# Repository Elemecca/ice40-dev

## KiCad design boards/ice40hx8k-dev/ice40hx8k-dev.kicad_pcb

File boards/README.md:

## Copying

Copyright 2022 Sam Hanes

The documentation in this directory describes Open Hardware and is
licensed under the CERN-OHL-S version 2 or any later version.

You may redistribute and modify this source and make products using it
under the terms of the [CERN-OHL-S v2](https://ohwr.org/cern_ohl_s_v2.txt).

This source is distributed WITHOUT ANY EXPRESS OR IMPLIED WARRANTY,
INCLUDING OF MERCHANTABILITY, SATISFACTORY QUALITY AND FITNESS FOR
A PARTICULAR PURPOSE. Please see the CERN-OHL-S v2 for applicable
conditions.

Source location: https://github.com/Elemecca/ice40-dev

As per CERN-OHL-S v2 section 4, should You produce hardware based
on this source, You must where practicable maintain the Source Location
visible on the external case of the products you make using this source.

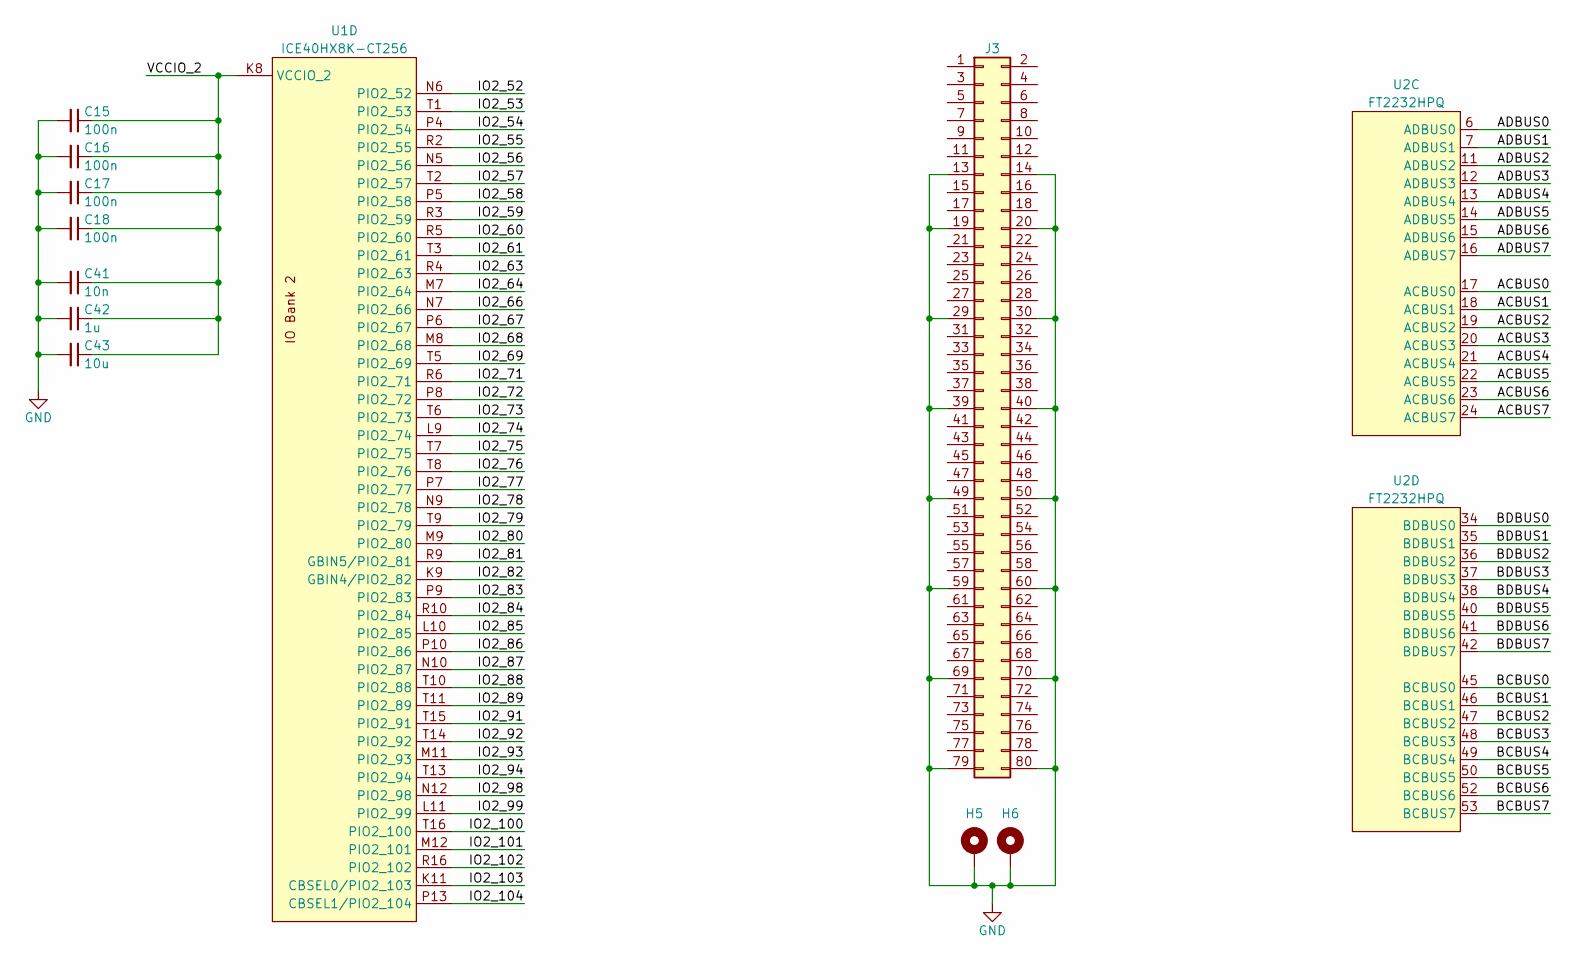
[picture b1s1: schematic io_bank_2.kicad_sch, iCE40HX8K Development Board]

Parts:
C15, C16, C17, C18: 100n; C_SMD_0402_Pad0.5mm
C41: 10n; C_SMD_0402_Pad0.5mm
C42: 1u; C_SMD_0402_Pad0.5mm
C43: 10u; C_SMD_0402_Pad0.5mm
H5, H6: 9774020633; MountingHole_2.2mm_M2_Pad6mm
J3: DF40HC(4.0)-80DS; Hirose_DF40C-80DS
U1: ICE40HX8K-CT256; Lattice_caBGA-256_14x14mm_Layout16x16_P0.8mm_Ball0.4mm_Pad0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
U2: FT2232HPQ; QFN-68-1EP_8x8mm_P0.4mm_EP5.2x5.2mm

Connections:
/IO_Bank_2/ACBUS0: U2.17 (ACBUS0)
/IO_Bank_2/ACBUS1: U2.18 (ACBUS1)
/IO_Bank_2/ACBUS2: U2.19 (ACBUS2)
/IO_Bank_2/ACBUS3: U2.20 (ACBUS3)
/IO_Bank_2/ACBUS4: U2.21 (ACBUS4)
/IO_Bank_2/ACBUS5: U2.22 (ACBUS5)
/IO_Bank_2/ACBUS6: U2.23 (ACBUS6)
/IO_Bank_2/ACBUS7: U2.24 (ACBUS7)
/IO_Bank_2/ADBUS0: U2.6 (ADBUS0)
/IO_Bank_2/ADBUS1: U2.7 (ADBUS1)
/IO_Bank_2/ADBUS2: U2.11 (ADBUS2)
/IO_Bank_2/ADBUS3: U2.12 (ADBUS3)
/IO_Bank_2/ADBUS4: U2.13 (ADBUS4)
/IO_Bank_2/ADBUS5: U2.14 (ADBUS5)
/IO_Bank_2/ADBUS6: U2.15 (ADBUS6)
/IO_Bank_2/ADBUS7: U2.16 (ADBUS7)
/IO_Bank_2/BCBUS0: U2.45 (BCBUS0)
/IO_Bank_2/BCBUS1: U2.46 (BCBUS1)
/IO_Bank_2/BCBUS2: U2.47 (BCBUS2)
/IO_Bank_2/BCBUS3: U2.48 (BCBUS3)
/IO_Bank_2/BCBUS4: U2.49 (BCBUS4)
/IO_Bank_2/BCBUS5: U2.50 (BCBUS5)
/IO_Bank_2/BCBUS6: U2.52 (BCBUS6)
/IO_Bank_2/BCBUS7: U2.53 (BCBUS7)
/IO_Bank_2/BDBUS0: U2.34 (BDBUS0)
/IO_Bank_2/BDBUS1: U2.35 (BDBUS1)
/IO_Bank_2/BDBUS2: U2.36 (BDBUS2)
/IO_Bank_2/BDBUS3: U2.37 (BDBUS3)
/IO_Bank_2/BDBUS4: U2.38 (BDBUS4)
/IO_Bank_2/BDBUS5: U2.40 (BDBUS5)
/IO_Bank_2/BDBUS6: U2.41 (BDBUS6)
/IO_Bank_2/BDBUS7: U2.42 (BDBUS7)
/IO_Bank_2/IO2_52: U1.N6 (PIO2_52)
/IO_Bank_2/IO2_53: U1.T1 (PIO2_53)
/IO_Bank_2/IO2_54: U1.P4 (PIO2_54)
/IO_Bank_2/IO2_55: U1.R2 (PIO2_55)
/IO_Bank_2/IO2_56: U1.N5 (PIO2_56)
/IO_Bank_2/IO2_57: U1.T2 (PIO2_57)
/IO_Bank_2/IO2_58: U1.P5 (PIO2_58)
/IO_Bank_2/IO2_59: U1.R3 (PIO2_59)
/IO_Bank_2/IO2_60: U1.R5 (PIO2_60)
/IO_Bank_2/IO2_61: U1.T3 (PIO2_61)
/IO_Bank_2/IO2_63: U1.R4 (PIO2_63)
/IO_Bank_2/IO2_64: U1.M7 (PIO2_64)
/IO_Bank_2/IO2_66: U1.N7 (PIO2_66)
/IO_Bank_2/IO2_67: U1.P6 (PIO2_67)
/IO_Bank_2/IO2_68: U1.M8 (PIO2_68)
/IO_Bank_2/IO2_69: U1.T5 (PIO2_69)
/IO_Bank_2/IO2_71: U1.R6 (PIO2_71)
/IO_Bank_2/IO2_72: U1.P8 (PIO2_72)
/IO_Bank_2/IO2_73: U1.T6 (PIO2_73)
/IO_Bank_2/IO2_74: U1.L9 (PIO2_74)
/IO_Bank_2/IO2_75: U1.T7 (PIO2_75)
/IO_Bank_2/IO2_76: U1.T8 (PIO2_76)
/IO_Bank_2/IO2_77: U1.P7 (PIO2_77)
/IO_Bank_2/IO2_78: U1.N9 (PIO2_78)
/IO_Bank_2/IO2_79: U1.T9 (PIO2_79)
/IO_Bank_2/IO2_80: U1.M9 (PIO2_80)
/IO_Bank_2/IO2_81: U1.R9 (GBIN5/PIO2_81)
/IO_Bank_2/IO2_82: U1.K9 (GBIN4/PIO2_82)
/IO_Bank_2/IO2_83: U1.P9 (PIO2_83)
/IO_Bank_2/IO2_84: U1.R10 (PIO2_84)
/IO_Bank_2/IO2_85: U1.L10 (PIO2_85)
/IO_Bank_2/IO2_86: U1.P10 (PIO2_86)
/IO_Bank_2/IO2_87: U1.N10 (PIO2_87)
/IO_Bank_2/IO2_88: U1.T10 (PIO2_88)
/IO_Bank_2/IO2_89: U1.T11 (PIO2_89)
/IO_Bank_2/IO2_91: U1.T15 (PIO2_91)
/IO_Bank_2/IO2_92: U1.T14 (PIO2_92)
/IO_Bank_2/IO2_93: U1.M11 (PIO2_93)
/IO_Bank_2/IO2_94: U1.T13 (PIO2_94)
/IO_Bank_2/IO2_98: U1.N12 (PIO2_98)
/IO_Bank_2/IO2_99: U1.L11 (PIO2_99)
/IO_Bank_2/IO2_100: U1.T16 (PIO2_100)
/IO_Bank_2/IO2_101: U1.M12 (PIO2_101)
/IO_Bank_2/IO2_102: U1.R16 (PIO2_102)
/IO_Bank_2/IO2_103: U1.K11 (CBSEL0/PIO2_103)
/IO_Bank_2/IO2_104: U1.P13 (CBSEL1/PIO2_104)
/IO_Bank_2/VCCIO_2: C15.1, C16.1, C17.1, C18.1, C41.1, C42.1, C43.1, U1.K8 (VCCIO_2), U1.P3 (VCCIO_2), U1.R8 (VCCIO_2), U1.R13 (VCCIO_2)
GND: C15.2, C16.2, C17.2, C18.2, C41.2, C42.2, C43.2, H5.1, H6.1, J3.13, J3.14, J3.19, J3.20, J3.29, J3.30, J3.39, J3.40, J3.49, J3.50, J3.59, J3.60, J3.69, J3.70, J3.79, J3.80; also elsewhere on the board

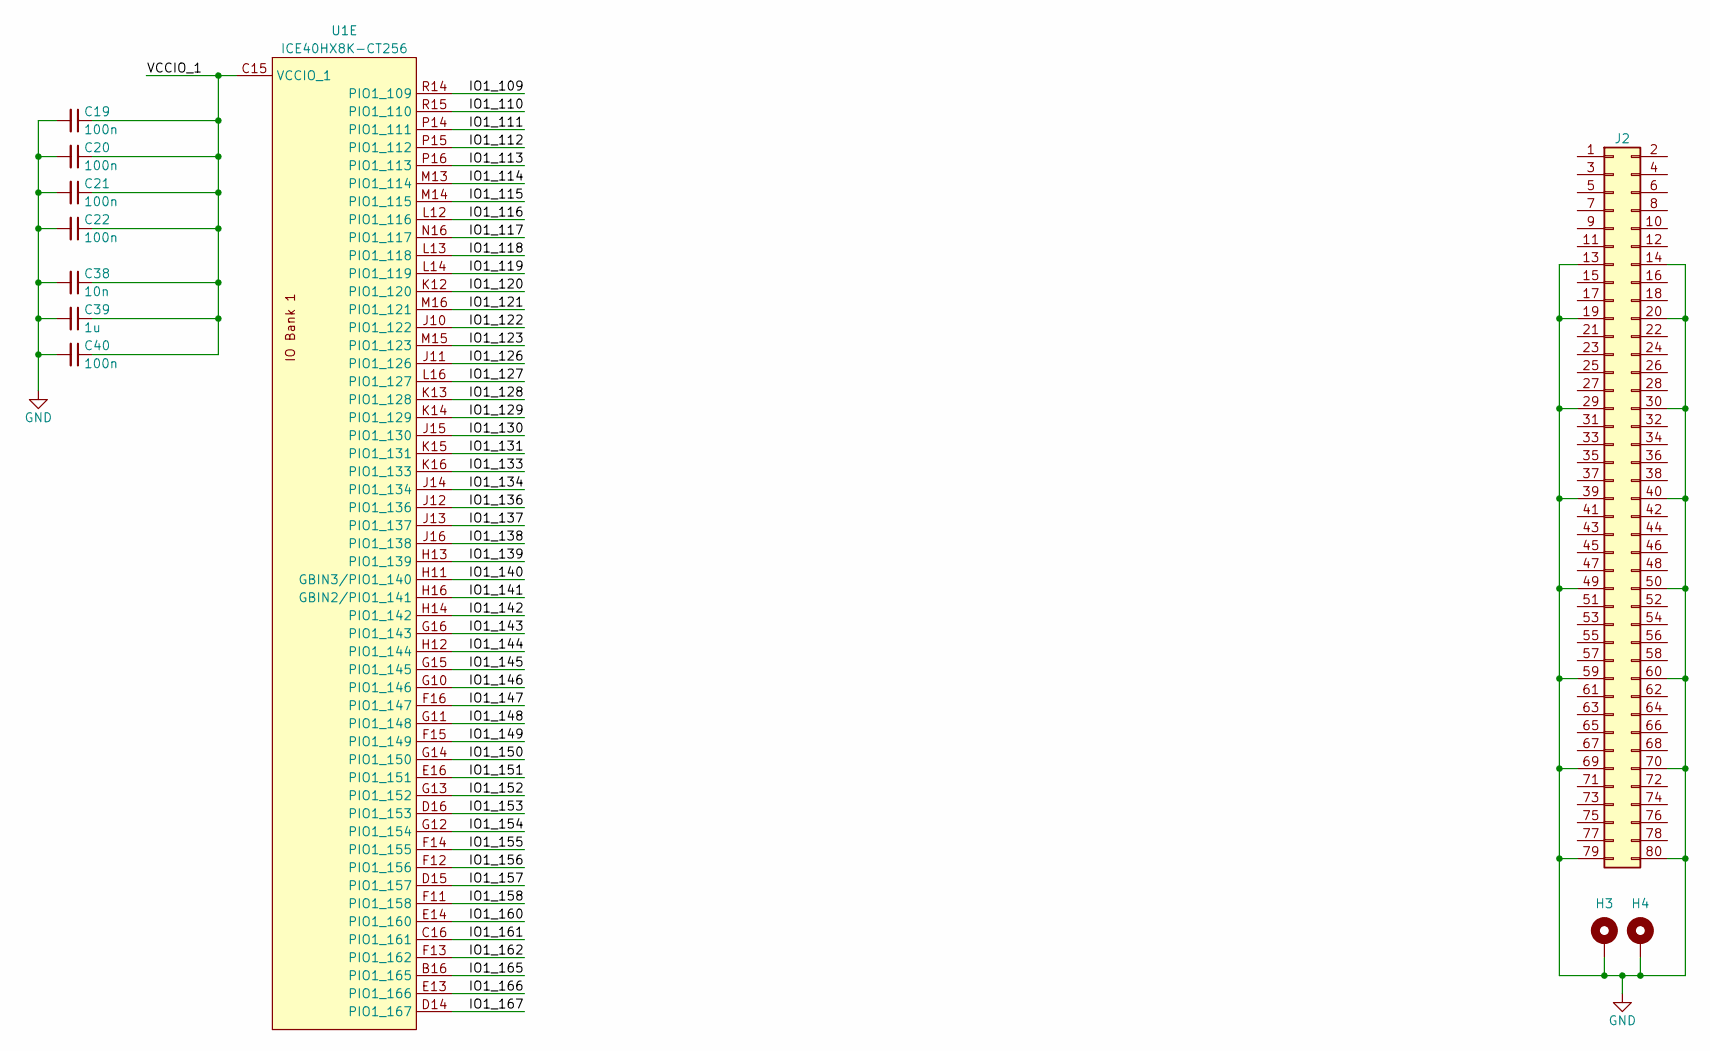
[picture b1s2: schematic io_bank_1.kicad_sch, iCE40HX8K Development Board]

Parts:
C19, C20, C21, C22, C40: 100n; C_SMD_0402_Pad0.5mm
C38: 10n; C_SMD_0402_Pad0.5mm
C39: 1u; C_SMD_0402_Pad0.5mm
H3, H4: 9774020633; MountingHole_2.2mm_M2_Pad6mm
J2: DF40HC(4.0)-80DS; Hirose_DF40C-80DS
U1: ICE40HX8K-CT256; Lattice_caBGA-256_14x14mm_Layout16x16_P0.8mm_Ball0.4mm_Pad0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

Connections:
/IO_Bank_1/IO1_109: U1.R14 (PIO1_109)
/IO_Bank_1/IO1_110: U1.R15 (PIO1_110)
/IO_Bank_1/IO1_111: U1.P14 (PIO1_111)
/IO_Bank_1/IO1_112: U1.P15 (PIO1_112)
/IO_Bank_1/IO1_113: U1.P16 (PIO1_113)
/IO_Bank_1/IO1_114: U1.M13 (PIO1_114)
/IO_Bank_1/IO1_115: U1.M14 (PIO1_115)
/IO_Bank_1/IO1_116: U1.L12 (PIO1_116)
/IO_Bank_1/IO1_117: U1.N16 (PIO1_117)
/IO_Bank_1/IO1_118: U1.L13 (PIO1_118)
/IO_Bank_1/IO1_119: U1.L14 (PIO1_119)
/IO_Bank_1/IO1_120: U1.K12 (PIO1_120)
/IO_Bank_1/IO1_121: U1.M16 (PIO1_121)
/IO_Bank_1/IO1_122: U1.J10 (PIO1_122)
/IO_Bank_1/IO1_123: U1.M15 (PIO1_123)
/IO_Bank_1/IO1_126: U1.J11 (PIO1_126)
/IO_Bank_1/IO1_127: U1.L16 (PIO1_127)
/IO_Bank_1/IO1_128: U1.K13 (PIO1_128)
/IO_Bank_1/IO1_129: U1.K14 (PIO1_129)
/IO_Bank_1/IO1_130: U1.J15 (PIO1_130)
/IO_Bank_1/IO1_131: U1.K15 (PIO1_131)
/IO_Bank_1/IO1_133: U1.K16 (PIO1_133)
/IO_Bank_1/IO1_134: U1.J14 (PIO1_134)
/IO_Bank_1/IO1_136: U1.J12 (PIO1_136)
/IO_Bank_1/IO1_137: U1.J13 (PIO1_137)
/IO_Bank_1/IO1_138: U1.J16 (PIO1_138)
/IO_Bank_1/IO1_139: U1.H13 (PIO1_139)
/IO_Bank_1/IO1_140: U1.H11 (GBIN3/PIO1_140)
/IO_Bank_1/IO1_141: U1.H16 (GBIN2/PIO1_141)
/IO_Bank_1/IO1_142: U1.H14 (PIO1_142)
/IO_Bank_1/IO1_143: U1.G16 (PIO1_143)
/IO_Bank_1/IO1_144: U1.H12 (PIO1_144)
/IO_Bank_1/IO1_145: U1.G15 (PIO1_145)
/IO_Bank_1/IO1_146: U1.G10 (PIO1_146)
/IO_Bank_1/IO1_147: U1.F16 (PIO1_147)
/IO_Bank_1/IO1_148: U1.G11 (PIO1_148)
/IO_Bank_1/IO1_149: U1.F15 (PIO1_149)
/IO_Bank_1/IO1_150: U1.G14 (PIO1_150)
/IO_Bank_1/IO1_151: U1.E16 (PIO1_151)
/IO_Bank_1/IO1_152: U1.G13 (PIO1_152)
/IO_Bank_1/IO1_153: U1.D16 (PIO1_153)
/IO_Bank_1/IO1_154: U1.G12 (PIO1_154)
/IO_Bank_1/IO1_155: U1.F14 (PIO1_155)
/IO_Bank_1/IO1_156: U1.F12 (PIO1_156)
/IO_Bank_1/IO1_157: U1.D15 (PIO1_157)
/IO_Bank_1/IO1_158: U1.F11 (PIO1_158)
/IO_Bank_1/IO1_160: U1.E14 (PIO1_160)
/IO_Bank_1/IO1_161: U1.C16 (PIO1_161)
/IO_Bank_1/IO1_162: U1.F13 (PIO1_162)
/IO_Bank_1/IO1_165: U1.B16 (PIO1_165)
/IO_Bank_1/IO1_166: U1.E13 (PIO1_166)
/IO_Bank_1/IO1_167: U1.D14 (PIO1_167)
/IO_Bank_1/VCCIO_1: C19.1, C20.1, C21.1, C22.1, C38.1, C39.1, C40.1, U1.C15 (VCCIO_1), U1.H10 (VCCIO_1), U1.H15 (VCCIO_1), U1.N15 (VCCIO_1)
GND: C19.2, C20.2, C21.2, C22.2, C38.2, C39.2, C40.2, H3.1, H4.1, J2.13, J2.14, J2.19, J2.20, J2.29, J2.30, J2.39, J2.40, J2.49, J2.50, J2.59, J2.60, J2.69, J2.70, J2.79, J2.80; also elsewhere on the board

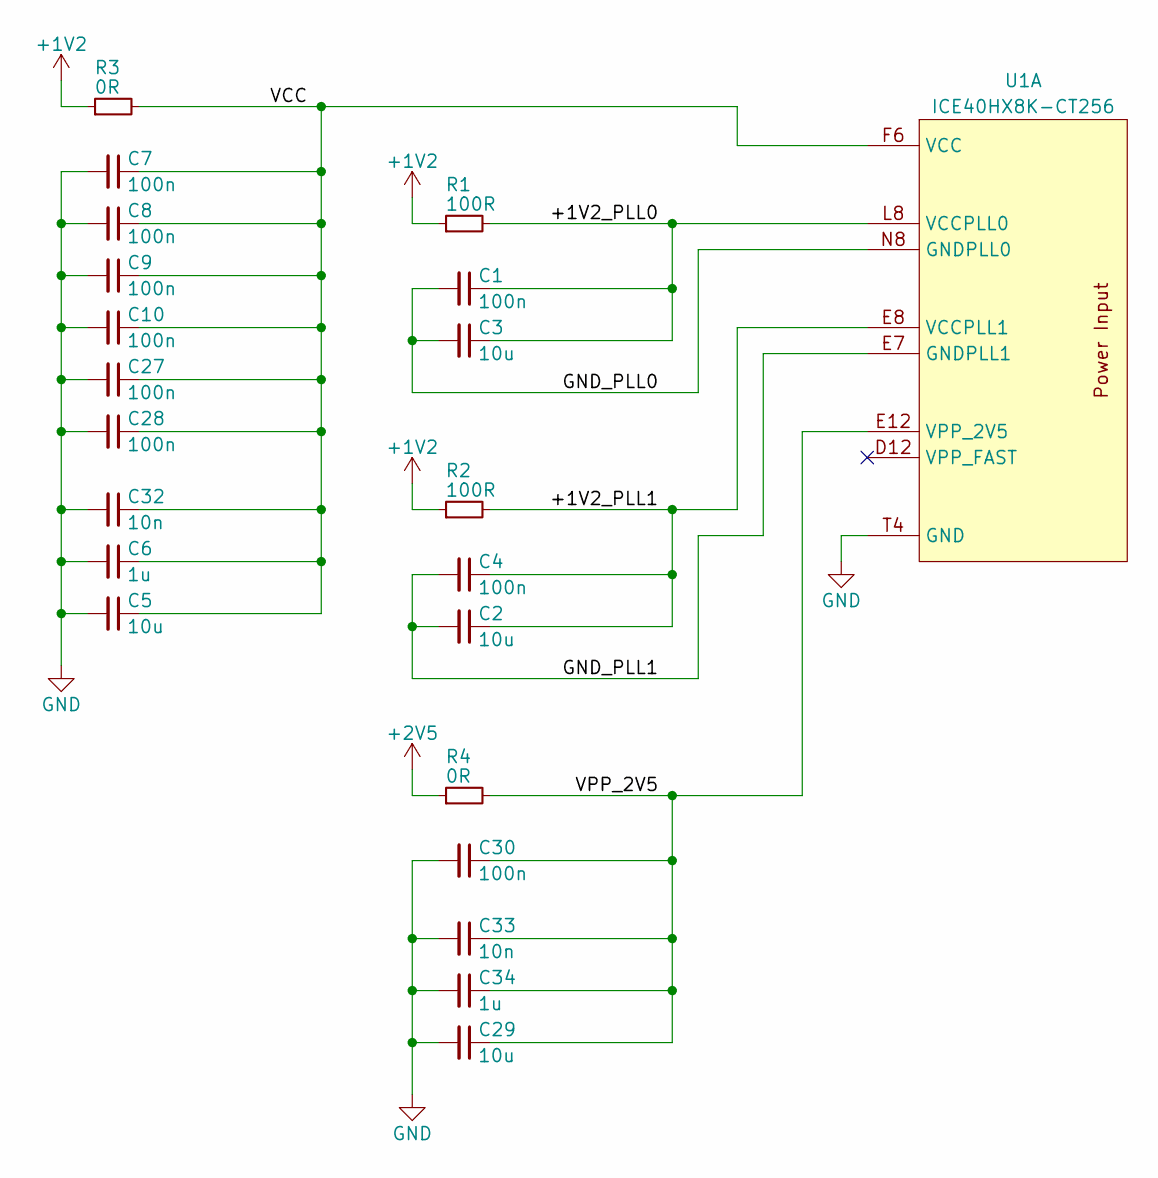
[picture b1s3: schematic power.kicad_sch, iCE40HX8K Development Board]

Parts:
C1, C4, C7, C8, C9, C10, C27, C28, C30: 100n; C_SMD_0402_Pad0.5mm
C2, C3, C5, C29: 10u; C_SMD_0402_Pad0.5mm
C6, C34: 1u; C_SMD_0402_Pad0.5mm
C32, C33: 10n; C_SMD_0402_Pad0.5mm
R1, R2: 100R; R_SMD_0402_Pad0.5mm
R3, R4: 0R; R_SMD_0402_Pad0.5mm
U1: ICE40HX8K-CT256; Lattice_caBGA-256_14x14mm_Layout16x16_P0.8mm_Ball0.4mm_Pad0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

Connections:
+1V2: R1.1, R2.1, R3.1
+2V5: R4.1
/Power/+1V2_PLL0: C1.1, C3.1, R1.2, U1.L8 (VCCPLL0)
/Power/+1V2_PLL1: C2.1, C4.1, R2.2, U1.E8 (VCCPLL1)
/Power/GND_PLL0: C1.2, C3.2, U1.N8 (GNDPLL0)
/Power/GND_PLL1: C2.2, C4.2, U1.E7 (GNDPLL1)
/Power/VCC: C5.1, C6.1, C7.1, C8.1, C9.1, C10.1, C27.1, C28.1, C32.1, R3.2, U1.A14 (VCC), U1.F6 (VCC), U1.F10 (VCC), U1.K6 (VCC), U1.K10 (VCC), U1.L2 (VCC)
/Power/VPP_2V5: C29.1, C30.1, C33.1, C34.1, R4.2, U1.E12 (VPP_2V5)
GND: C5.2, C6.2, C7.2, C8.2, C9.2, C10.2, C27.2, C28.2, C29.2, C30.2, C32.2, C33.2, C34.2, U1.A4 (GND), U1.A12 (GND), U1.E15 (GND), U1.G7 (GND), U1.G8 (GND), U1.G9 (GND), U1.H7 (GND), U1.H8 (GND), U1.H9 (GND), U1.J7 (GND), U1.J8 (GND), U1.J9 (GND), U1.K2 (GND), U1.K7 (GND), U1.L15 (GND), U1.R7 (GND), U1.T4 (GND), U1.T12 (GND); also elsewhere on the board

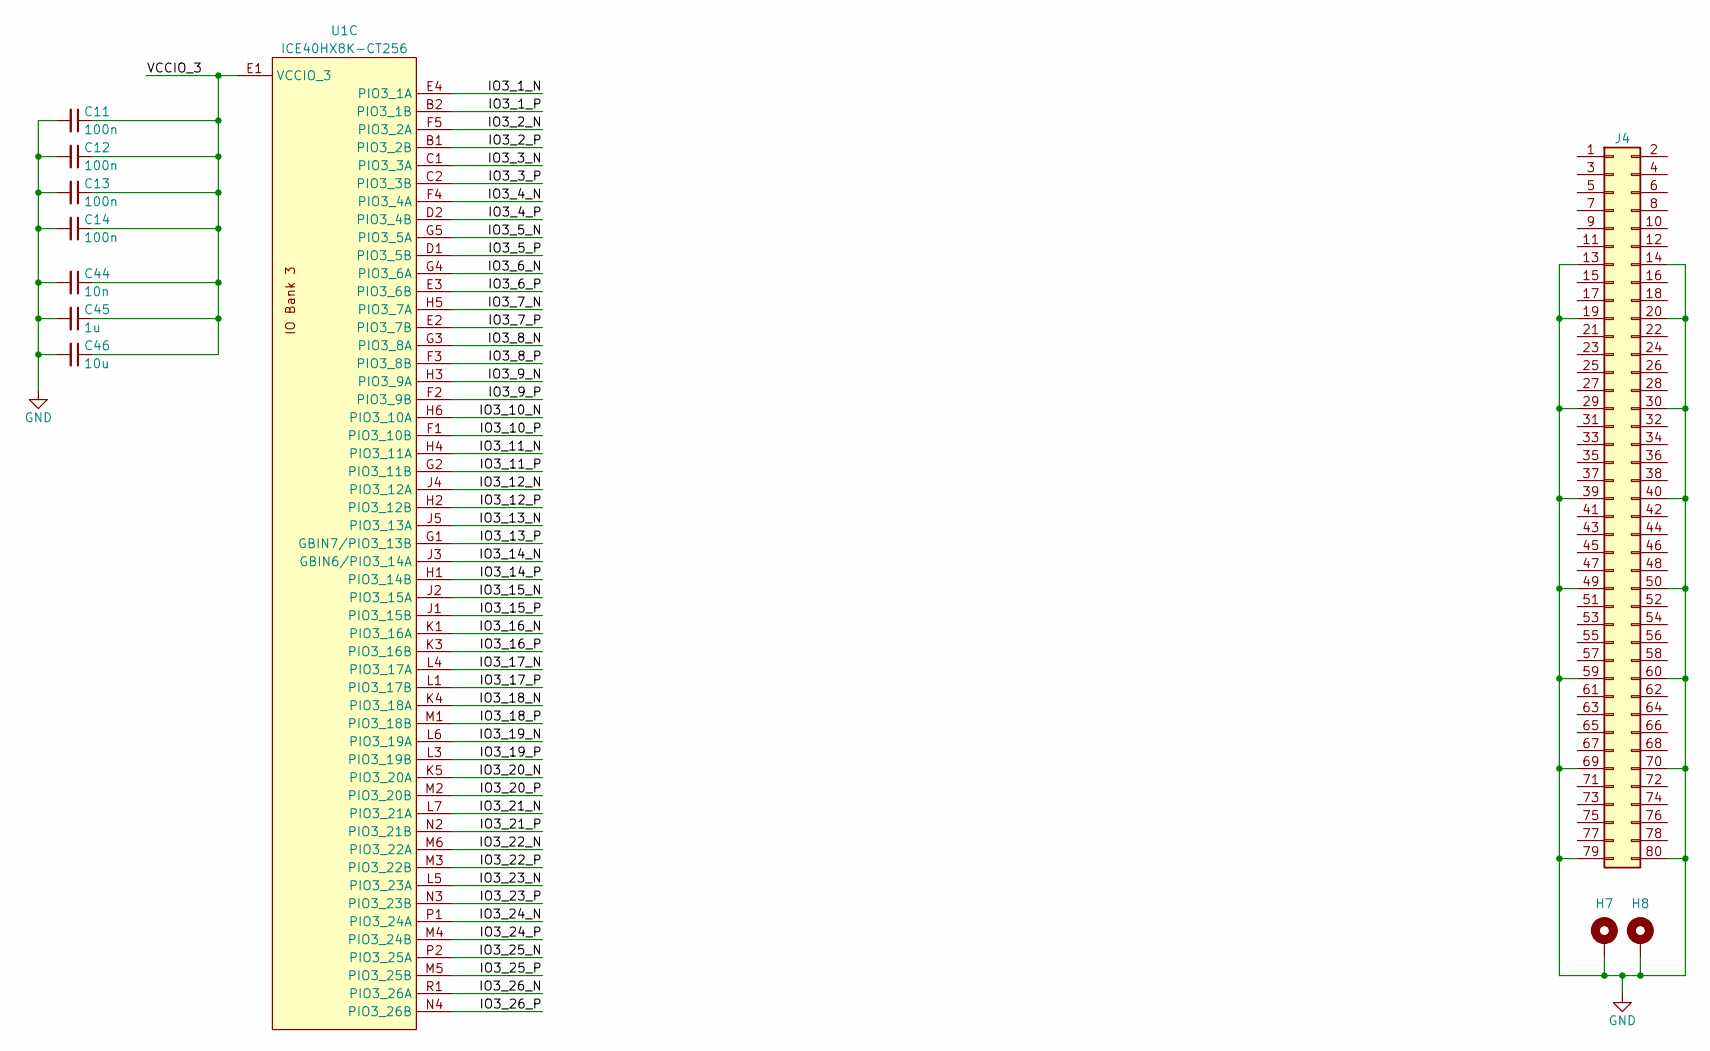
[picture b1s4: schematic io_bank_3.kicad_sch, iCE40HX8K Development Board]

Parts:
C11, C12, C13, C14: 100n; C_SMD_0402_Pad0.5mm
C44: 10n; C_SMD_0402_Pad0.5mm
C45: 1u; C_SMD_0402_Pad0.5mm
C46: 10u; C_SMD_0402_Pad0.5mm
H7, H8: 9774020633; MountingHole_2.2mm_M2_Pad6mm
J4: DF40HC(4.0)-80DS; Hirose_DF40C-80DS
U1: ICE40HX8K-CT256; Lattice_caBGA-256_14x14mm_Layout16x16_P0.8mm_Ball0.4mm_Pad0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

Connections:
/IO_Bank_3/IO3_1_N: U1.E4 (PIO3_1A)
/IO_Bank_3/IO3_1_P: U1.B2 (PIO3_1B)
/IO_Bank_3/IO3_2_N: U1.F5 (PIO3_2A)
/IO_Bank_3/IO3_2_P: U1.B1 (PIO3_2B)
/IO_Bank_3/IO3_3_N: U1.C1 (PIO3_3A)
/IO_Bank_3/IO3_3_P: U1.C2 (PIO3_3B)
/IO_Bank_3/IO3_4_N: U1.F4 (PIO3_4A)
/IO_Bank_3/IO3_4_P: U1.D2 (PIO3_4B)
/IO_Bank_3/IO3_5_N: U1.G5 (PIO3_5A)
/IO_Bank_3/IO3_5_P: U1.D1 (PIO3_5B)
/IO_Bank_3/IO3_6_N: U1.G4 (PIO3_6A)
/IO_Bank_3/IO3_6_P: U1.E3 (PIO3_6B)
/IO_Bank_3/IO3_7_N: U1.H5 (PIO3_7A)
/IO_Bank_3/IO3_7_P: U1.E2 (PIO3_7B)
/IO_Bank_3/IO3_8_N: U1.G3 (PIO3_8A)
/IO_Bank_3/IO3_8_P: U1.F3 (PIO3_8B)
/IO_Bank_3/IO3_9_N: U1.H3 (PIO3_9A)
/IO_Bank_3/IO3_9_P: U1.F2 (PIO3_9B)
/IO_Bank_3/IO3_10_N: U1.H6 (PIO3_10A)
/IO_Bank_3/IO3_10_P: U1.F1 (PIO3_10B)
/IO_Bank_3/IO3_11_N: U1.H4 (PIO3_11A)
/IO_Bank_3/IO3_11_P: U1.G2 (PIO3_11B)
/IO_Bank_3/IO3_12_N: U1.J4 (PIO3_12A)
/IO_Bank_3/IO3_12_P: U1.H2 (PIO3_12B)
/IO_Bank_3/IO3_13_N: U1.J5 (PIO3_13A)
/IO_Bank_3/IO3_13_P: U1.G1 (GBIN7/PIO3_13B)
/IO_Bank_3/IO3_14_N: U1.J3 (GBIN6/PIO3_14A)
/IO_Bank_3/IO3_14_P: U1.H1 (PIO3_14B)
/IO_Bank_3/IO3_15_N: U1.J2 (PIO3_15A)
/IO_Bank_3/IO3_15_P: U1.J1 (PIO3_15B)
/IO_Bank_3/IO3_16_N: U1.K1 (PIO3_16A)
/IO_Bank_3/IO3_16_P: U1.K3 (PIO3_16B)
/IO_Bank_3/IO3_17_N: U1.L4 (PIO3_17A)
/IO_Bank_3/IO3_17_P: U1.L1 (PIO3_17B)
/IO_Bank_3/IO3_18_N: U1.K4 (PIO3_18A)
/IO_Bank_3/IO3_18_P: U1.M1 (PIO3_18B)
/IO_Bank_3/IO3_19_N: U1.L6 (PIO3_19A)
/IO_Bank_3/IO3_19_P: U1.L3 (PIO3_19B)
/IO_Bank_3/IO3_20_N: U1.K5 (PIO3_20A)
/IO_Bank_3/IO3_20_P: U1.M2 (PIO3_20B)
/IO_Bank_3/IO3_21_N: U1.L7 (PIO3_21A)
/IO_Bank_3/IO3_21_P: U1.N2 (PIO3_21B)
/IO_Bank_3/IO3_22_N: U1.M6 (PIO3_22A)
/IO_Bank_3/IO3_22_P: U1.M3 (PIO3_22B)
/IO_Bank_3/IO3_23_N: U1.L5 (PIO3_23A)
/IO_Bank_3/IO3_23_P: U1.N3 (PIO3_23B)
/IO_Bank_3/IO3_24_N: U1.P1 (PIO3_24A)
/IO_Bank_3/IO3_24_P: U1.M4 (PIO3_24B)
/IO_Bank_3/IO3_25_N: U1.P2 (PIO3_25A)
/IO_Bank_3/IO3_25_P: U1.M5 (PIO3_25B)
/IO_Bank_3/IO3_26_N: U1.R1 (PIO3_26A)
/IO_Bank_3/IO3_26_P: U1.N4 (PIO3_26B)
/IO_Bank_3/VCCIO_3: C11.1, C12.1, C13.1, C14.1, C44.1, C45.1, C46.1, U1.E1 (VCCIO_3), U1.G6 (VCCIO_3), U1.J6 (VCCIO_3), U1.N1 (VCCIO_3)
GND: C11.2, C12.2, C13.2, C14.2, C44.2, C45.2, C46.2, H7.1, H8.1, J4.13, J4.14, J4.19, J4.20, J4.29, J4.30, J4.39, J4.40, J4.49, J4.50, J4.59, J4.60, J4.69, J4.70, J4.79, J4.80; also elsewhere on the board

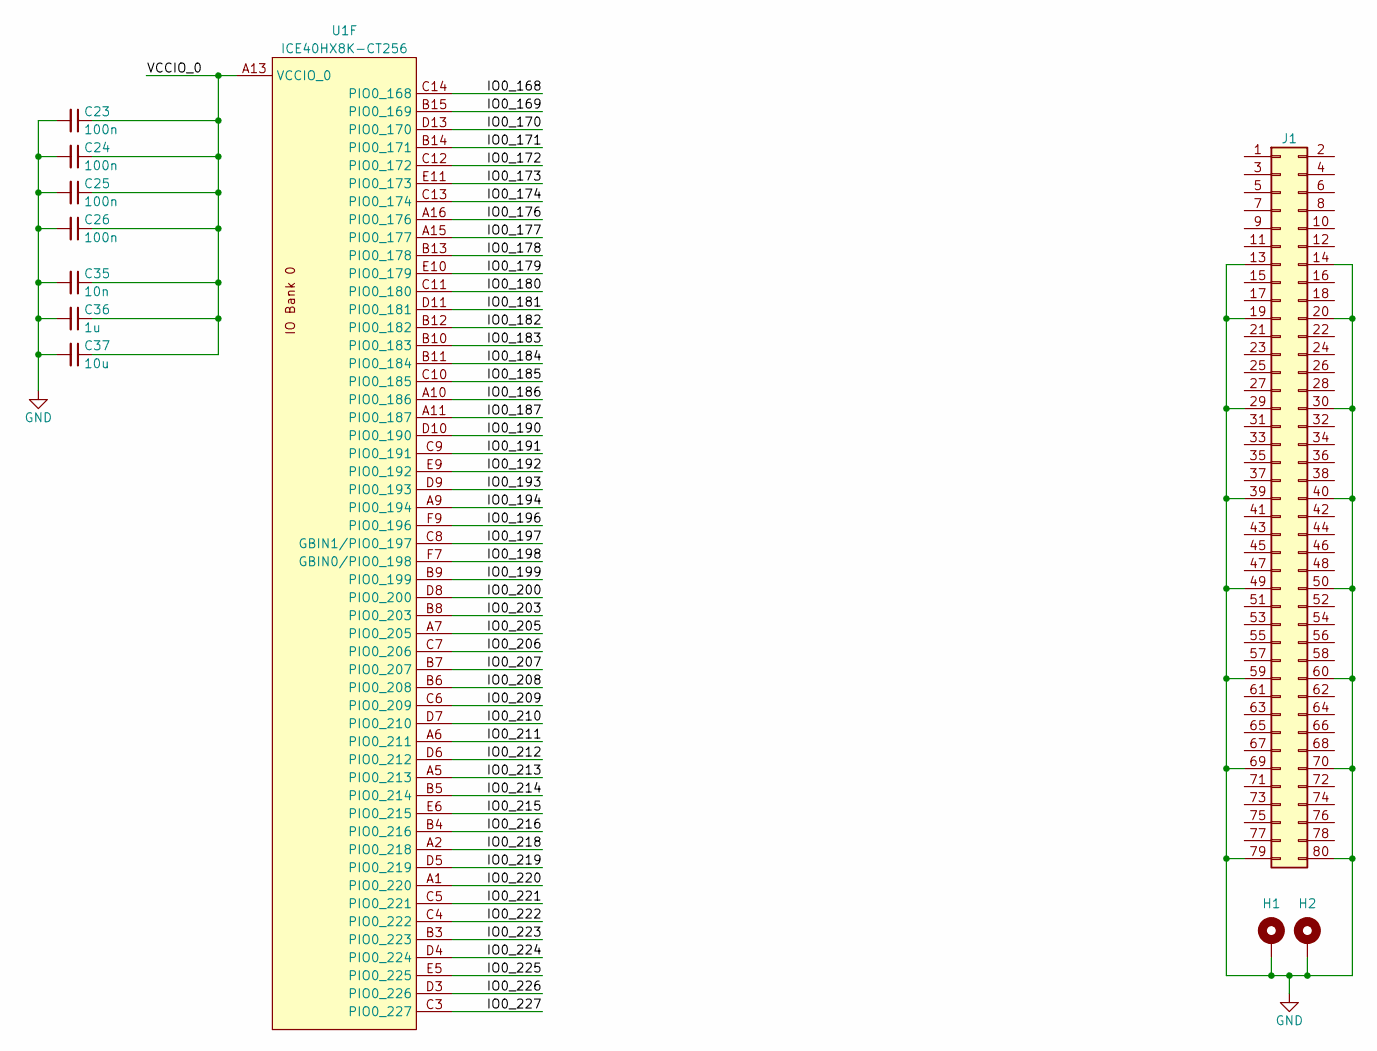
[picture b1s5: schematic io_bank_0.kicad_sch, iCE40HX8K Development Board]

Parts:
C23, C24, C25, C26: 100n; C_SMD_0402_Pad0.5mm
C35: 10n; C_SMD_0402_Pad0.5mm
C36: 1u; C_SMD_0402_Pad0.5mm
C37: 10u; C_SMD_0402_Pad0.5mm
H1, H2: 9774020633; MountingHole_2.2mm_M2_Pad6mm
J1: DF40HC(4.0)-80DS; Hirose_DF40C-80DS
U1: ICE40HX8K-CT256; Lattice_caBGA-256_14x14mm_Layout16x16_P0.8mm_Ball0.4mm_Pad0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

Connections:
/IO_Bank_0/IO0_168: U1.C14 (PIO0_168)
/IO_Bank_0/IO0_169: U1.B15 (PIO0_169)
/IO_Bank_0/IO0_170: U1.D13 (PIO0_170)
/IO_Bank_0/IO0_171: U1.B14 (PIO0_171)
/IO_Bank_0/IO0_172: U1.C12 (PIO0_172)
/IO_Bank_0/IO0_173: U1.E11 (PIO0_173)
/IO_Bank_0/IO0_174: U1.C13 (PIO0_174)
/IO_Bank_0/IO0_176: U1.A16 (PIO0_176)
/IO_Bank_0/IO0_177: U1.A15 (PIO0_177)
/IO_Bank_0/IO0_178: U1.B13 (PIO0_178)
/IO_Bank_0/IO0_179: U1.E10 (PIO0_179)
/IO_Bank_0/IO0_180: U1.C11 (PIO0_180)
/IO_Bank_0/IO0_181: U1.D11 (PIO0_181)
/IO_Bank_0/IO0_182: U1.B12 (PIO0_182)
/IO_Bank_0/IO0_183: U1.B10 (PIO0_183)
/IO_Bank_0/IO0_184: U1.B11 (PIO0_184)
/IO_Bank_0/IO0_185: U1.C10 (PIO0_185)
/IO_Bank_0/IO0_186: U1.A10 (PIO0_186)
/IO_Bank_0/IO0_187: U1.A11 (PIO0_187)
/IO_Bank_0/IO0_190: U1.D10 (PIO0_190)
/IO_Bank_0/IO0_191: U1.C9 (PIO0_191)
/IO_Bank_0/IO0_192: U1.E9 (PIO0_192)
/IO_Bank_0/IO0_193: U1.D9 (PIO0_193)
/IO_Bank_0/IO0_194: U1.A9 (PIO0_194)
/IO_Bank_0/IO0_196: U1.F9 (PIO0_196)
/IO_Bank_0/IO0_197: U1.C8 (GBIN1/PIO0_197)
/IO_Bank_0/IO0_198: U1.F7 (GBIN0/PIO0_198)
/IO_Bank_0/IO0_199: U1.B9 (PIO0_199)
/IO_Bank_0/IO0_200: U1.D8 (PIO0_200)
/IO_Bank_0/IO0_203: U1.B8 (PIO0_203)
/IO_Bank_0/IO0_205: U1.A7 (PIO0_205)
/IO_Bank_0/IO0_206: U1.C7 (PIO0_206)
/IO_Bank_0/IO0_207: U1.B7 (PIO0_207)
/IO_Bank_0/IO0_208: U1.B6 (PIO0_208)
/IO_Bank_0/IO0_209: U1.C6 (PIO0_209)
/IO_Bank_0/IO0_210: U1.D7 (PIO0_210)
/IO_Bank_0/IO0_211: U1.A6 (PIO0_211)
/IO_Bank_0/IO0_212: U1.D6 (PIO0_212)
/IO_Bank_0/IO0_213: U1.A5 (PIO0_213)
/IO_Bank_0/IO0_214: U1.B5 (PIO0_214)
/IO_Bank_0/IO0_215: U1.E6 (PIO0_215)
/IO_Bank_0/IO0_216: U1.B4 (PIO0_216)
/IO_Bank_0/IO0_218: U1.A2 (PIO0_218)
/IO_Bank_0/IO0_219: U1.D5 (PIO0_219)
/IO_Bank_0/IO0_220: U1.A1 (PIO0_220)
/IO_Bank_0/IO0_221: U1.C5 (PIO0_221)
/IO_Bank_0/IO0_222: U1.C4 (PIO0_222)
/IO_Bank_0/IO0_223: U1.B3 (PIO0_223)
/IO_Bank_0/IO0_224: U1.D4 (PIO0_224)
/IO_Bank_0/IO0_225: U1.E5 (PIO0_225)
/IO_Bank_0/IO0_226: U1.D3 (PIO0_226)
/IO_Bank_0/IO0_227: U1.C3 (PIO0_227)
/IO_Bank_0/VCCIO_0: C23.1, C24.1, C25.1, C26.1, C35.1, C36.1, C37.1, U1.A3 (VCCIO_0), U1.A8 (VCCIO_0), U1.A13 (VCCIO_0), U1.F8 (VCCIO_0)
GND: C23.2, C24.2, C25.2, C26.2, C35.2, C36.2, C37.2, H1.1, H2.1, J1.13, J1.14, J1.19, J1.20, J1.29, J1.30, J1.39, J1.40, J1.49, J1.50, J1.59, J1.60, J1.69, J1.70, J1.79, J1.80; also elsewhere on the board

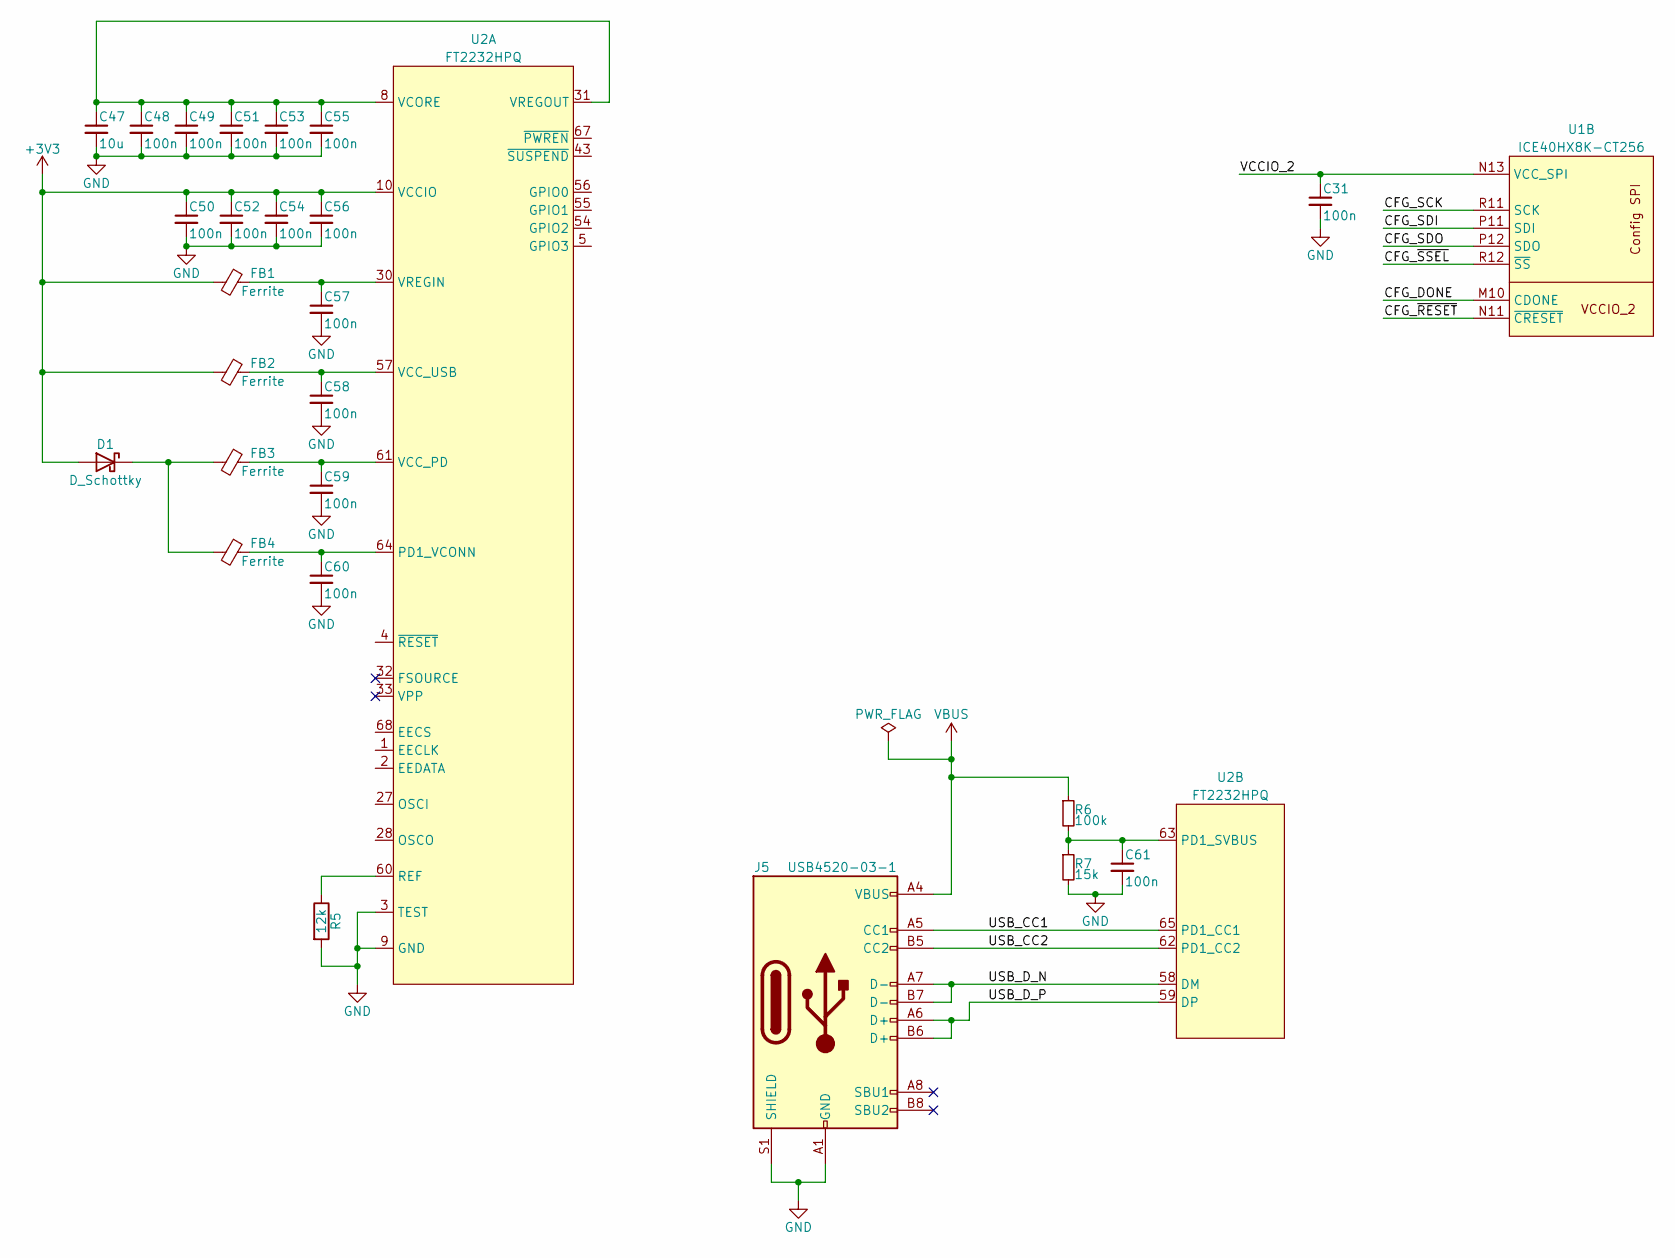
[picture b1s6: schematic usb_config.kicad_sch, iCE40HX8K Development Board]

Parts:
C31, C48, C49, C50, C51, C52, C53, C54, C55, C56, C57, C58, C59, C60, C61: 100n; C_SMD_0402_Pad0.5mm
C47: 10u; C_SMD_0402_Pad0.5mm
D1: D_Schottky; D_0603_1608Metric
FB1, FB2, FB3, FB4: Ferrite
J5: USB4520-03-1; GCT_USB45xx
R5: 12k; R_0603_1608Metric
R6: 100k; R_0603_1608Metric
R7: 15k; R_0603_1608Metric
U1: ICE40HX8K-CT256; Lattice_caBGA-256_14x14mm_Layout16x16_P0.8mm_Ball0.4mm_Pad0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
U2: FT2232HPQ; QFN-68-1EP_8x8mm_P0.4mm_EP5.2x5.2mm

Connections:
+3V3: C50.1, C52.1, C54.1, C56.1, D1.2 (A), FB1.2, FB2.2, U2.10 (VCCIO), U2.26 (VCCIO), U2.39 (VCCIO), U2.51 (VCCIO)
/USB_Config/CFG_DONE: U1.M10 (CDONE)
/USB_Config/CFG_SCK: U1.R11 (SCK)
/USB_Config/CFG_SDI: U1.P11 (SDI)
/USB_Config/CFG_SDO: U1.P12 (SDO)
/USB_Config/CFG_~RESET: U1.N11 (~CRESET)
/USB_Config/CFG_~SSEL: U1.R12 (~SS)
/USB_Config/USB_CC1: J5.A5 (CC1), U2.65 (PD1_CC1)
/USB_Config/USB_CC2: J5.B5 (CC2), U2.62 (PD1_CC2)
/USB_Config/USB_D_N: J5.A7 (D-), J5.B7 (D-), U2.58 (DM)
/USB_Config/USB_D_P: J5.A6 (D+), J5.B6 (D+), U2.59 (DP)
/USB_Config/VCCIO_2: C31.1, U1.N13 (VCC_SPI)
GND: C31.2, C47.2, C48.2, C49.2, C50.2, C51.2, C52.2, C53.2, C54.2, C55.2, C56.2, C57.2, C58.2, C59.2, C60.2, C61.2, J5.A1 (GND), J5.A12 (GND), J5.B1 (GND), J5.B12 (GND), J5.S1 (SHIELD), R5.2, R7.2, U2.3 (TEST), U2.9 (GND), U2.29 (GND); also elsewhere on the board
unnamed: C47.1, C48.1, C49.1, C51.1, C53.1, C55.1, U2.8 (VCORE), U2.25 (VCORE), U2.31 (VREGOUT), U2.44 (VCORE), U2.66 (VCORE)
unnamed: C57.1, FB1.1, U2.30 (VREGIN)
unnamed: C58.1, FB2.1, U2.57 (VCC_USB)
unnamed: C59.1, FB3.1, U2.61 (VCC_PD)
unnamed: C60.1, FB4.1, U2.64 (PD1_VCONN)
unnamed: C61.1, R6.2, R7.1, U2.63 (PD1_SVBUS)
unnamed: D1.1 (K), FB3.2, FB4.2
unnamed: R5.1, U2.60 (REF)
VBUS: J5.A4 (VBUS), J5.A9 (VBUS), J5.B4 (VBUS), J5.B9 (VBUS), R6.1

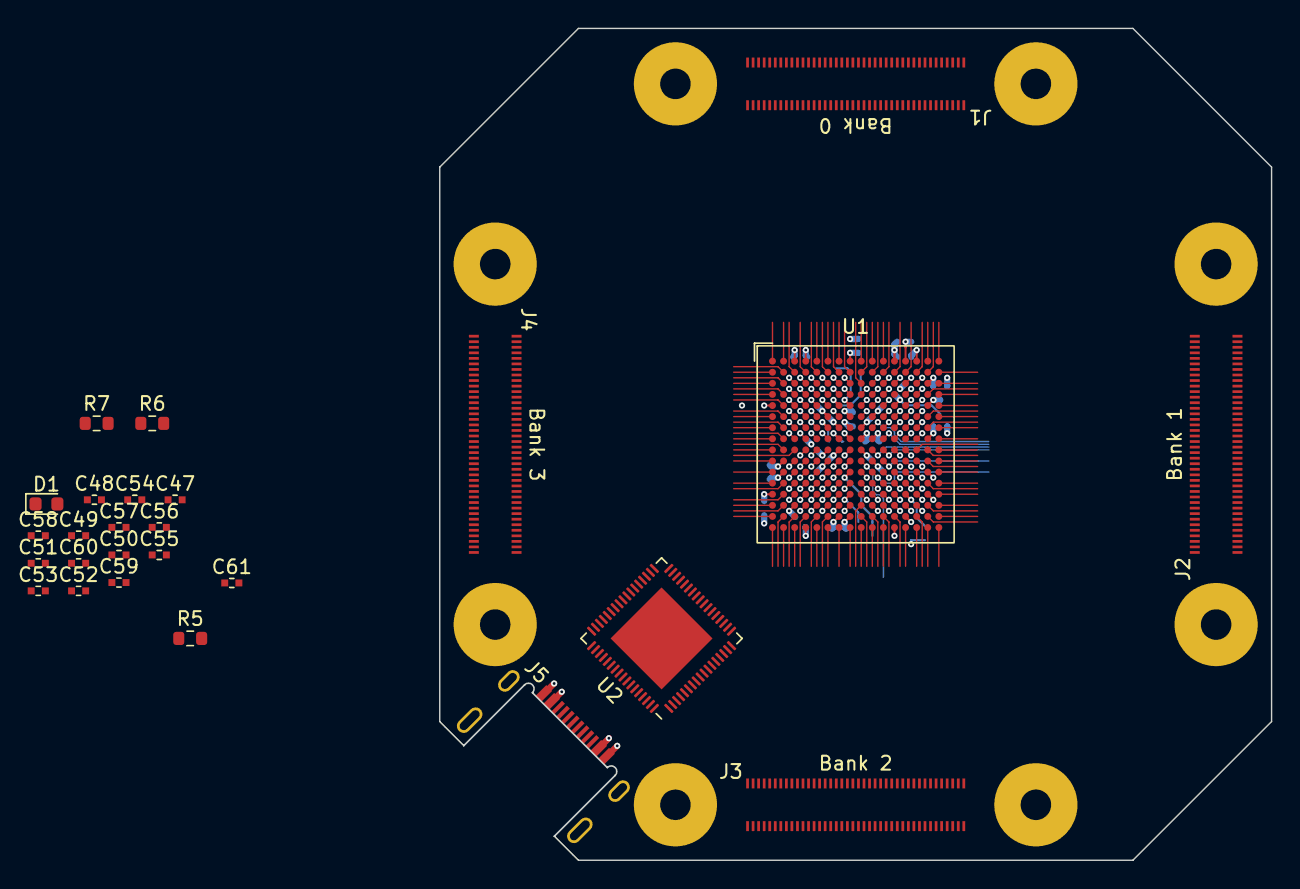
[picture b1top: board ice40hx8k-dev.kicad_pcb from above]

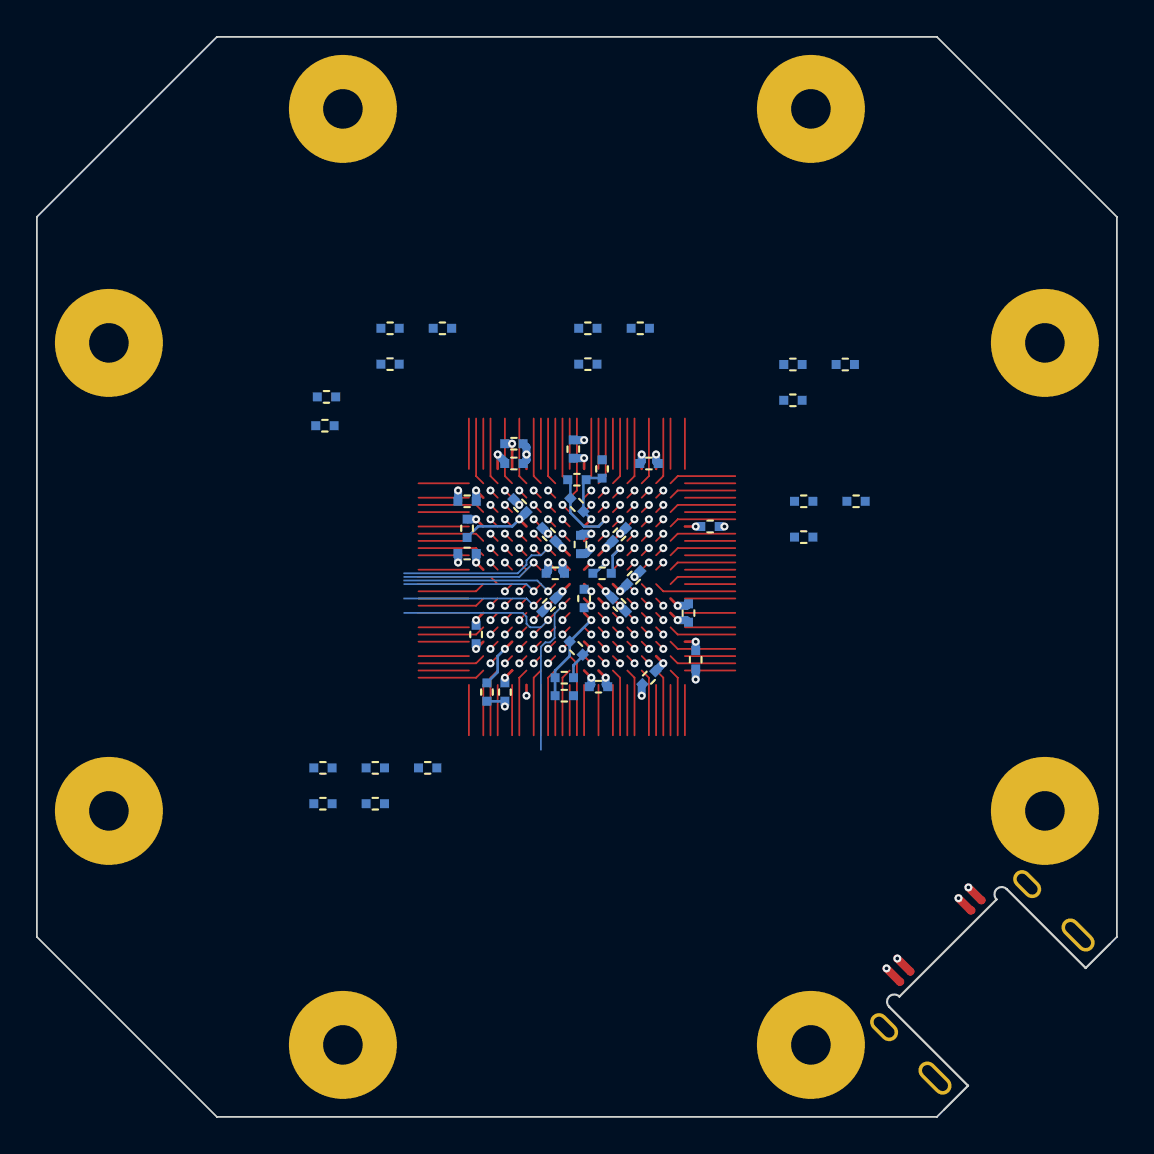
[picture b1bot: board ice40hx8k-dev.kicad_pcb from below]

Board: 6 copper layers, 60.0 x 60.0 mm, 84 parts (50 on the bottom side), 26 nets.

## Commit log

2022-05-01 Start with FPGA footprint and decoupling.
2022-05-01 Fan out all signal pads.
2022-05-02 Split up schematic and label all nets.
2022-10-13 Switch to 6 layers, add power fills under BGA.
2022-10-13 Add USB connector and FT2323 symbol.
2022-10-13 Use a lower-profile version of the USB connector.
2022-10-14 Add Hirose connectors and standoffs.
2022-10-14 Switch to 4mm Hirose connectors and different mounting holes.

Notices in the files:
boards/ice40hx8k-dev/ice40hx8k-dev.kicad_pcb:
© 2022 Sam Hanes, licensed under CERN-OHL-S v2+
